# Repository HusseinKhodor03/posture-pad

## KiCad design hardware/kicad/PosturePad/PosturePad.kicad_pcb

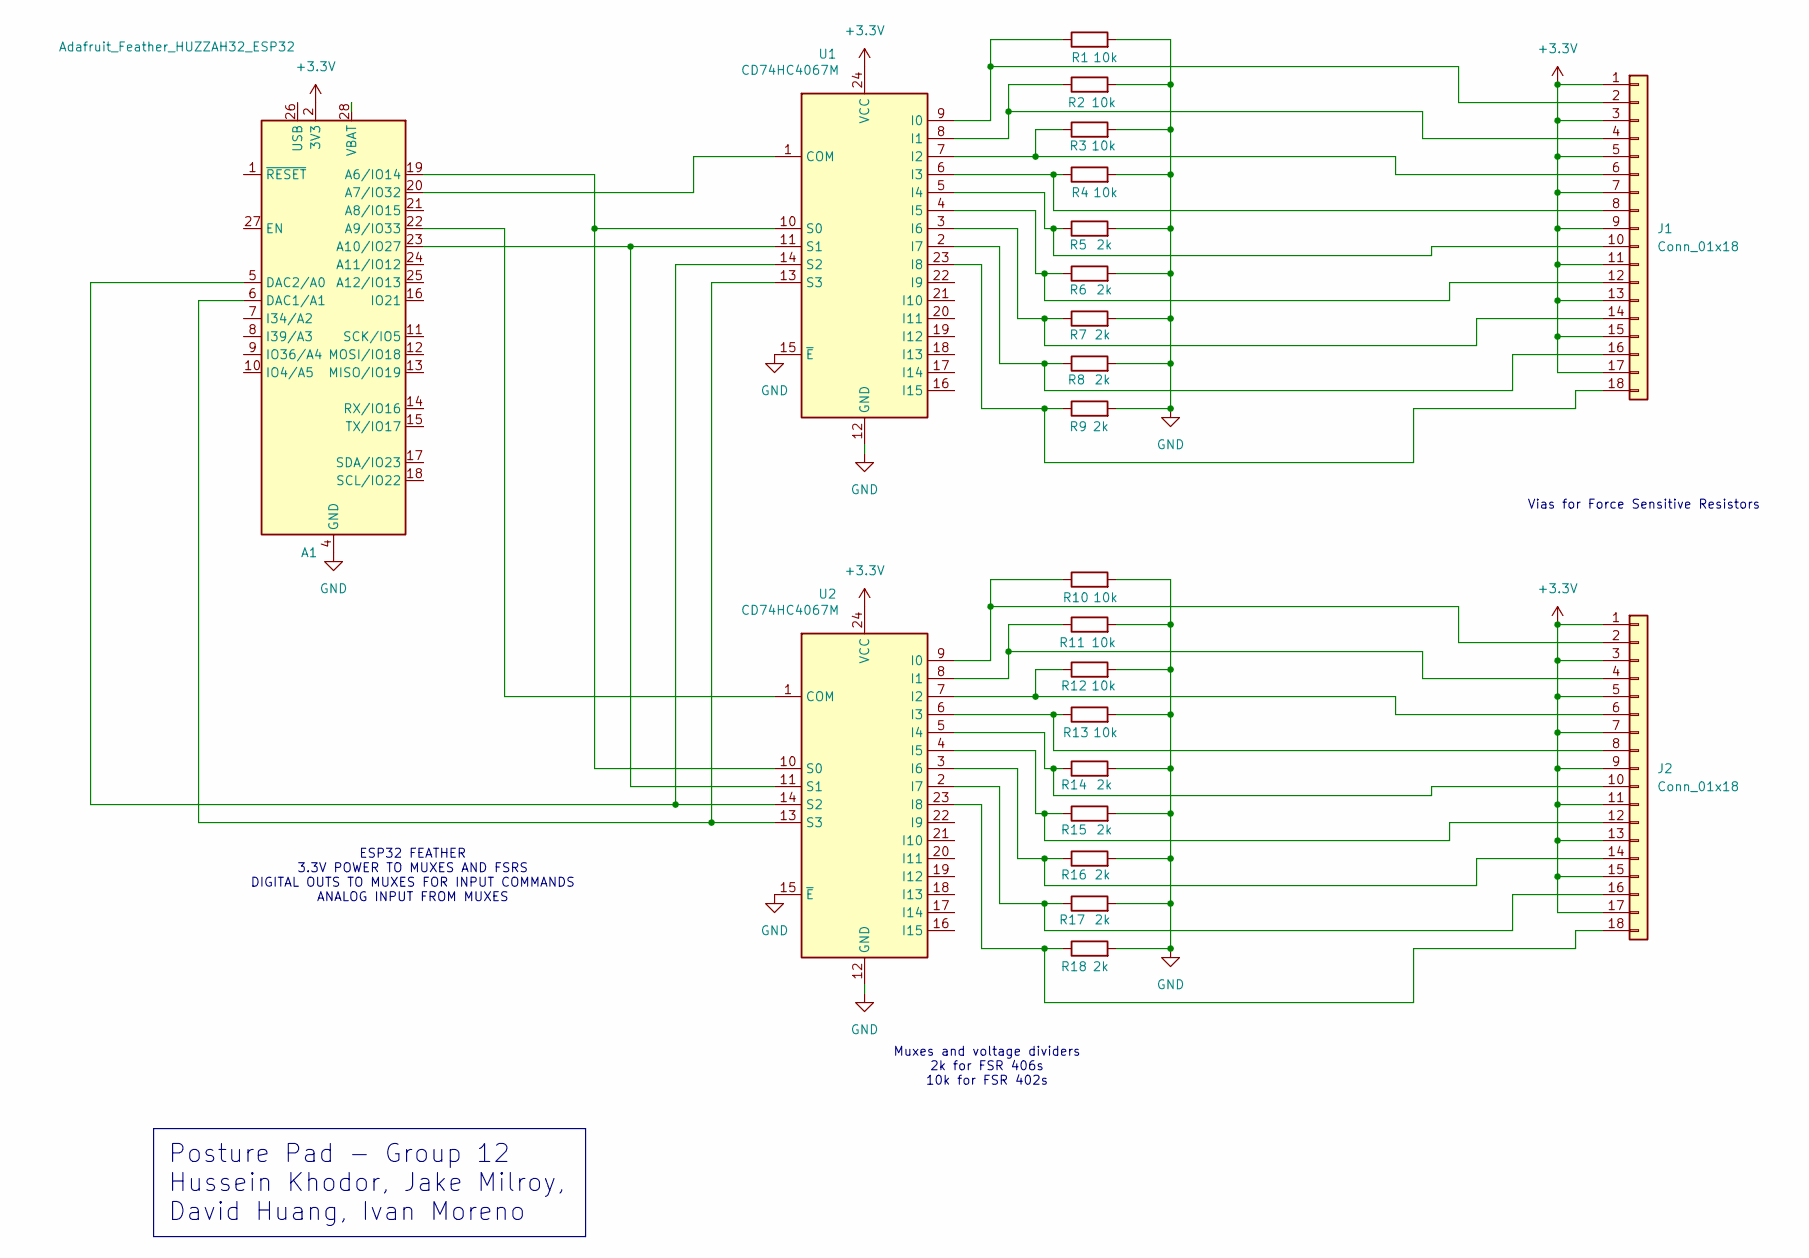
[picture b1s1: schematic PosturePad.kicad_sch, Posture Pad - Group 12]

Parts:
A1: Adafruit_Feather_HUZZAH32_ESP32; Adafruit_Feather_WithMountingHoles
J1, J2: Conn_01x18; PinHeader_1x18_P2.54mm_Vertical
R1, R2, R3, R4, R10, R11, R12, R13: 10k; R_0603_1608Metric
R5, R6, R7, R8, R9, R14, R15, R16, R17, R18: 2k; R_0603_1608Metric
U1, U2: CD74HC4067M; SOIC-24W_7.5x15.4mm_P1.27mm

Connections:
+3.3V: A1.2 (3V3), J1.1, J1.3, J1.5, J1.7, J1.9, J1.11, J1.13, J1.15, J1.17, J2.1, J2.3, J2.5, J2.7, J2.9, J2.11, J2.13, J2.15, J2.17, U1.24 (VCC), U2.24 (VCC)
GND: A1.4 (GND), R1.2, R2.2, R3.2, R4.2, R5.2, R6.2, R7.2, R8.2, R9.2, R10.2, R11.2, R12.2, R13.2, R14.2, R15.2, R16.2, R17.2, R18.2, U1.12 (GND), U1.15 (~E), U2.12 (GND), U2.15 (~E)
unnamed: A1.19 (A6/IO14), U1.10 (S0), U2.10 (S0)
unnamed: A1.20 (A7/IO32), U1.1 (COM)
unnamed: A1.22 (A9/IO33), U2.1 (COM)
unnamed: A1.23 (A10/IO27), U1.11 (S1), U2.11 (S1)
unnamed: A1.6 (DAC1/A1), U1.13 (S3), U2.13 (S3)
unnamed: A1.5 (DAC2/A0), U1.14 (S2), U2.14 (S2)
unnamed: J1.2, R1.1, U1.9 (I0)
unnamed: J1.4, R2.1, U1.8 (I1)
unnamed: J1.6, R3.1, U1.7 (I2)
unnamed: J1.8, R4.1, U1.6 (I3)
unnamed: J1.10, R5.1, U1.5 (I4)
unnamed: J1.12, R6.1, U1.4 (I5)
unnamed: J1.14, R7.1, U1.3 (I6)
unnamed: J1.16, R8.1, U1.2 (I7)
unnamed: J1.18, R9.1, U1.23 (I8)
unnamed: J2.2, R10.1, U2.9 (I0)
unnamed: J2.4, R11.1, U2.8 (I1)
unnamed: J2.6, R12.1, U2.7 (I2)
unnamed: J2.8, R13.1, U2.6 (I3)
unnamed: J2.10, R14.1, U2.5 (I4)
unnamed: J2.12, R15.1, U2.4 (I5)
unnamed: J2.14, R16.1, U2.3 (I6)
unnamed: J2.16, R17.1, U2.2 (I7)
unnamed: J2.18, R18.1, U2.23 (I8)

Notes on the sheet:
Posture Pad - Group 12 Hussein Khodor, Jake Milroy, David Huang, Ivan Moreno
Muxes and voltage dividers 2k for FSR 406s 10k for FSR 402s
Vias for Force Sensitive Resistors
ESP32 FEATHER 3.3V POWER TO MUXES AND FSRS DIGITAL OUTS TO MUXES FOR INPUT COMMANDS ANALOG INPUT FROM MUXES

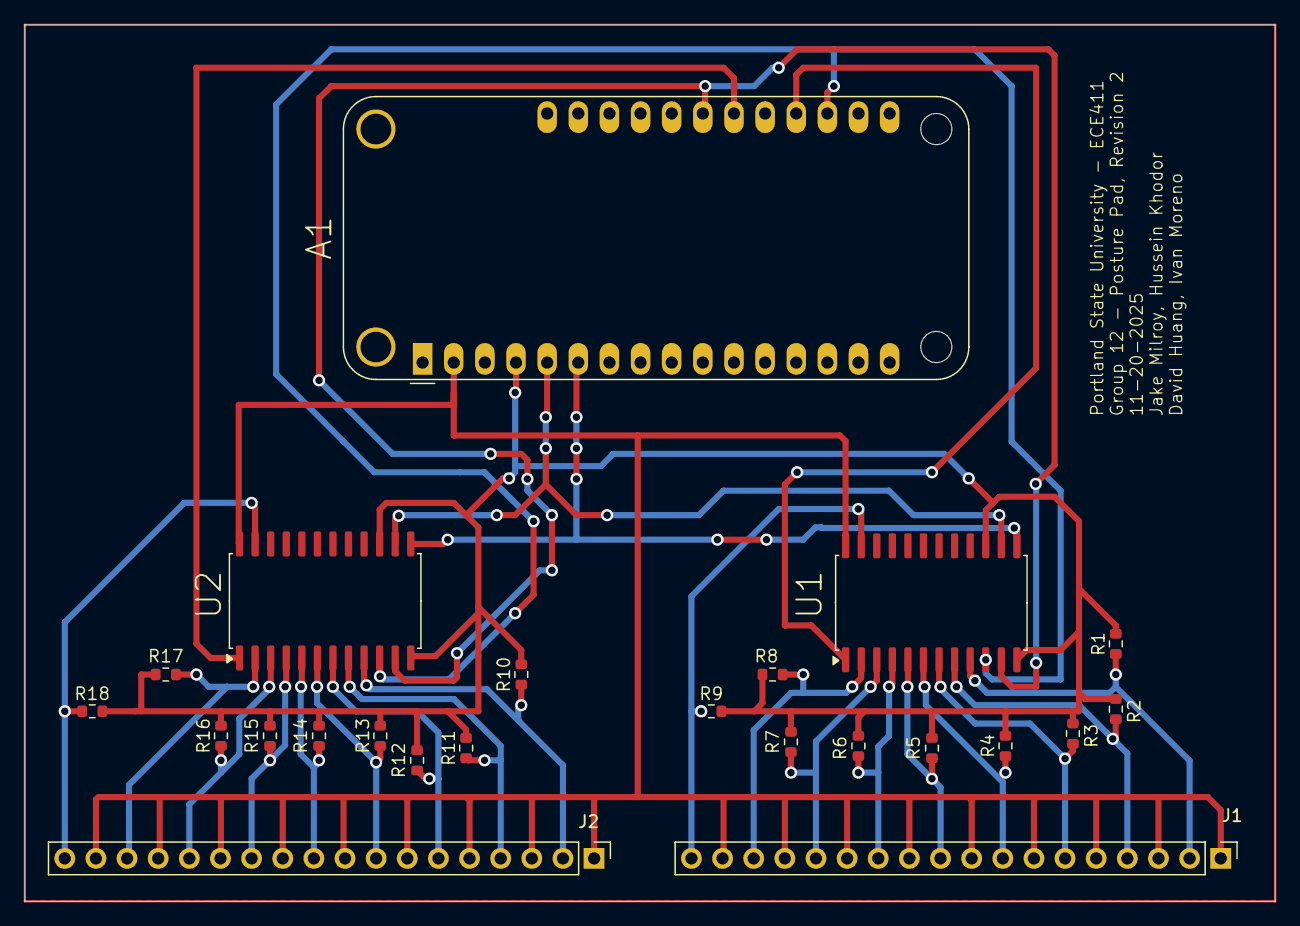
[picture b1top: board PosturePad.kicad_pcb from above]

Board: 2 copper layers, 102.0 x 71.5 mm, 23 parts (0 on the bottom side), 26 nets.

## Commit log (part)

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2025-10-23 Rename project from 'project-undecided' to 'posture-pad'
2025-10-24 Added the Practicum Product Design Specification document
2025-11-03 Added the Make a Decision document
2025-11-04 Added the preliminary schematic document
2025-11-06 Added the Gantt chart documents
2025-11-15 Added the bill of materials document
2025-11-15 Added the functional decomposition document
2025-11-19 Added the breadboard prototype document
2025-11-20 Added the updated schematic document
2025-11-22 Added the PCB CAD design
2025-11-22 Moved the breadboard prototype image from docs folder to hardware folder
2025-11-22 Removed old posturepad kicad files
2025-11-22 Added a kicad folder with the kicad project files as well as the gerber and drill files
2025-12-04 Added the first part of the test plan document
2025-12-04 Added the second part of the test plan document
2026-06-21 Added ESP32 firmware and posture pad dashboard
